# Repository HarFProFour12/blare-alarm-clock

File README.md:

# BLARE Alarm Clock

This is my custom alarm clock built using a Seeed XIAO ESP32C3 as the brain, with a customizable menu system, real-time clock over wifi, and public domain alarm melodies (Fur Elise, Mountain King, Reveille) played using a passive buzzer.

## Features

* RTC using Wi-Fi (NTP)
* Adjustable alarm time
* Changeable alarm sounds
* Adjustable font color
* Button-controlled UI
*  2.25in TFT Screen

## UI

The UI is designed using simple menus so it's easier to navigate using only four buttons (enter, back, up, down). 

The Home screen displays the current time.

The Settings menu currently has:

* Alarm Time
* Alarm Sound
* Font Color

## How It Works

The clock is controlled by a Seeed XIAO ESP32C3. On startup, it connects to the wifi and get the current time through NTP, since I couldn't use an RTC module (all available GPIO pins were already being used). The current time is displayed on the Home screen, and the user can set the alarm time through the Settings menu. When the current time is the same as the alarm time, the selected melody is played using the piezo buzzer.

## Hardware

The current hardware includes the following components:

* Seeed XIAO ESP32C3
* 2.25in TFT Screen (ST7789 driver)
* 4 pushbuttons
* Passive piezo buzzer

## Schematic & Hardware Wiring

The board uses the XIAO ESP32-C3's D0–D10 pins for all peripherals:

* D0–D3: pushbuttons (enter, back, up, down)
* D4–D6, D8–D10: TFT screen (DC, CS, BL, RST, SCL, SDA)
* D7: buzzer

All 11 available GPIOs are used, leaving no free pins for other components such as an RTC module.

The PCB was designed in KiCad, with the four pushbuttons placed alongside the screen for easy access.

## Project Structure

```text
BLARE/
├── main.ino
└── wifi_codes.h
```

## Current Status

The project is still in the making process.

What I've done so far:

* Basic TFT interface
* Home screen with live clock
* Menu navigation
* Settings screen
* Alarm time adjustment
* Font color adjustment
* Alarm sound selection
* Time sync over wifi
* Alarm trigger logic
* Snooze/dismiss handling

I have left to do:

* Hardware testing on the assembled PCB

## Design

The UI layout was designed using **lopaka.app**, an online graphic design tool for microcontroller screens, before being integrated into the Arduino sketch.

## Built With

* Arduino (C++)
* ESP32
* Adafruit_GFX / Adafruit_ST7789 (Arduino Libraries)
* lopaka.app
* KiCad

## AI Usage

I used AI, mainly for:

- Code debugging: fixing errors and syntax issues.
- Alarm sounds: adding public domain melodies (Für Elise, Reveille, In the Hall of the Mountain King) to play through the buzzer.

The actual project design, schematic, PCB layout, UI design, and final assembly were done by me.

---
**Made by Harry Fanouriakis**

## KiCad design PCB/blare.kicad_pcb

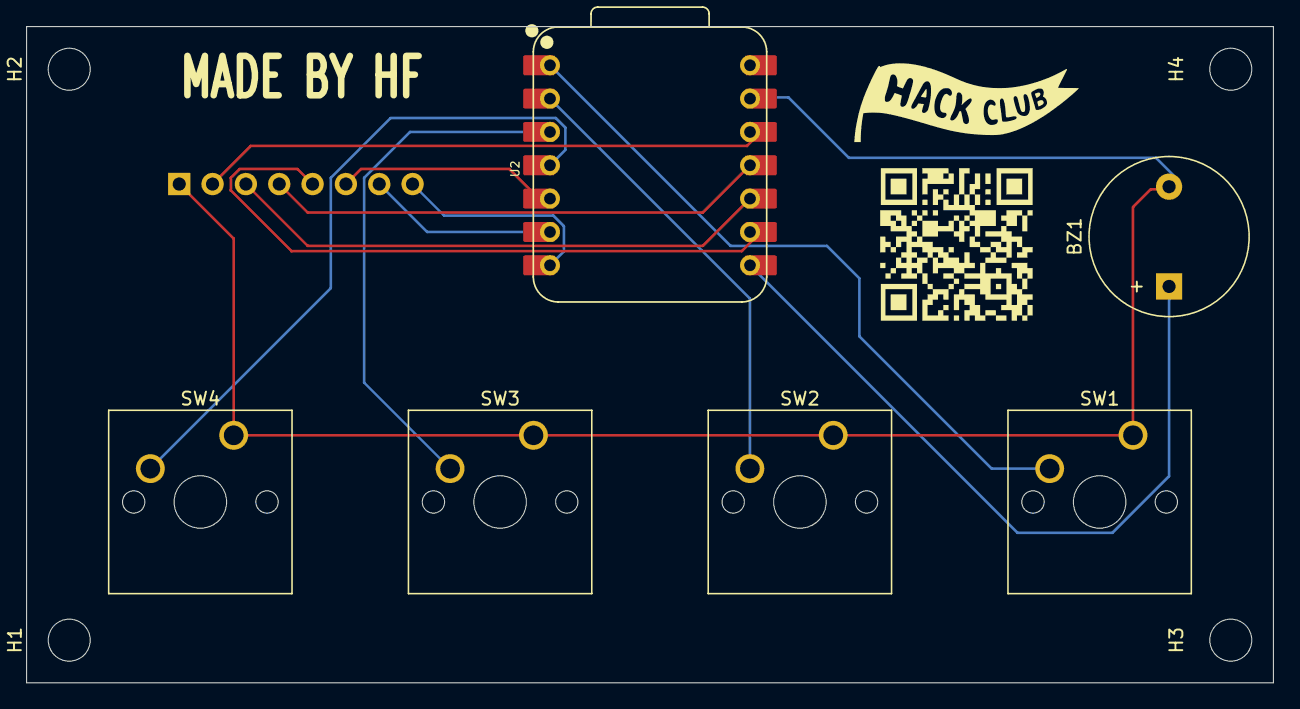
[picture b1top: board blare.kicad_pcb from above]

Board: 2 copper layers, 95.0 x 50.0 mm, 11 parts (1 on the bottom side), 13 nets.

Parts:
BZ1: Buzzer; Buzzer_12x9.5RM7.6
H1, H2, H3, H4: MountingHole; MountingHole_3.2mm_M3
J1: Conn_01x08_Pin; PinSocket_1x08_P2.54mm_Vertical
SW1, SW2, SW3, SW4: SW_Push; SW_Cherry_MX_1.00u_PCB
U2: XIAO-ESP32-C3-SMD; XIAO-ESP32-C3-DIP

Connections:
+3.3V: J1.2, U2.12 (3V3_OUT)
/BL: J1.8, U2.7 (D6)
/CS: J1.7, U2.6 (D5)
/DC: J1.6, U2.5 (D4)
/RST: J1.5, U2.9 (D8)
/SCL: J1.3, U2.10 (D9/BOOT)
/SDA: J1.4, U2.11 (D10)
GND: BZ1.2 (-), J1.1, SW1.1, SW2.1, SW3.1, SW4.1, U2.13 (GND)
unnamed: BZ1.1 (+), U2.8 (D7)
unnamed: SW1.2, U2.1 (D0)
unnamed: SW2.2, U2.2 (D1)
unnamed: SW3.2, U2.3 (D2)
unnamed: SW4.2, U2.4 (D3)
